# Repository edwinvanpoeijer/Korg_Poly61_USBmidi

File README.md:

# Korg_Poly61_USBmidi
USB Midi conversion for the Korg Poly61 synthesizer

This midi conversion uses a Teensy V3.2 to interface between the keys, arpeggiator and the cpu board.
This will add the following functionality to your Korg Poly61:

USB Midi interface
Hardware MIDI input
Hardware MIDI thru (from the hardware MIDI input)
Hardware MIDI out/thru (forwarded from the USB midi) 
MIDI synced arpeggiator (can be set to internal,  1/4, 1/8, 1/16, 1/32)
SYNC/TRIGGER out 
MIDI port selectable (1 - 16 or OMNI)

The MIDI port and arpeggiator sync can be set at power on by holding the keys.
C0  = ARP internal
C#0 = ARP 1/4
D0  = ARP 1/8
D#0 = ARP 1/16
E0  = ARP 1/32

C2 = MIDI channel 1 ---> D#3 = MIDI channel 16
E3 = OMNI

I have included the code, schematic and a very raw pcb (i still have some available).
There is a lot of space between the components and the pcb could be half it's current size :)
You will need a Teensy 3.1/3.2 for this as these are still 5V tolerant.

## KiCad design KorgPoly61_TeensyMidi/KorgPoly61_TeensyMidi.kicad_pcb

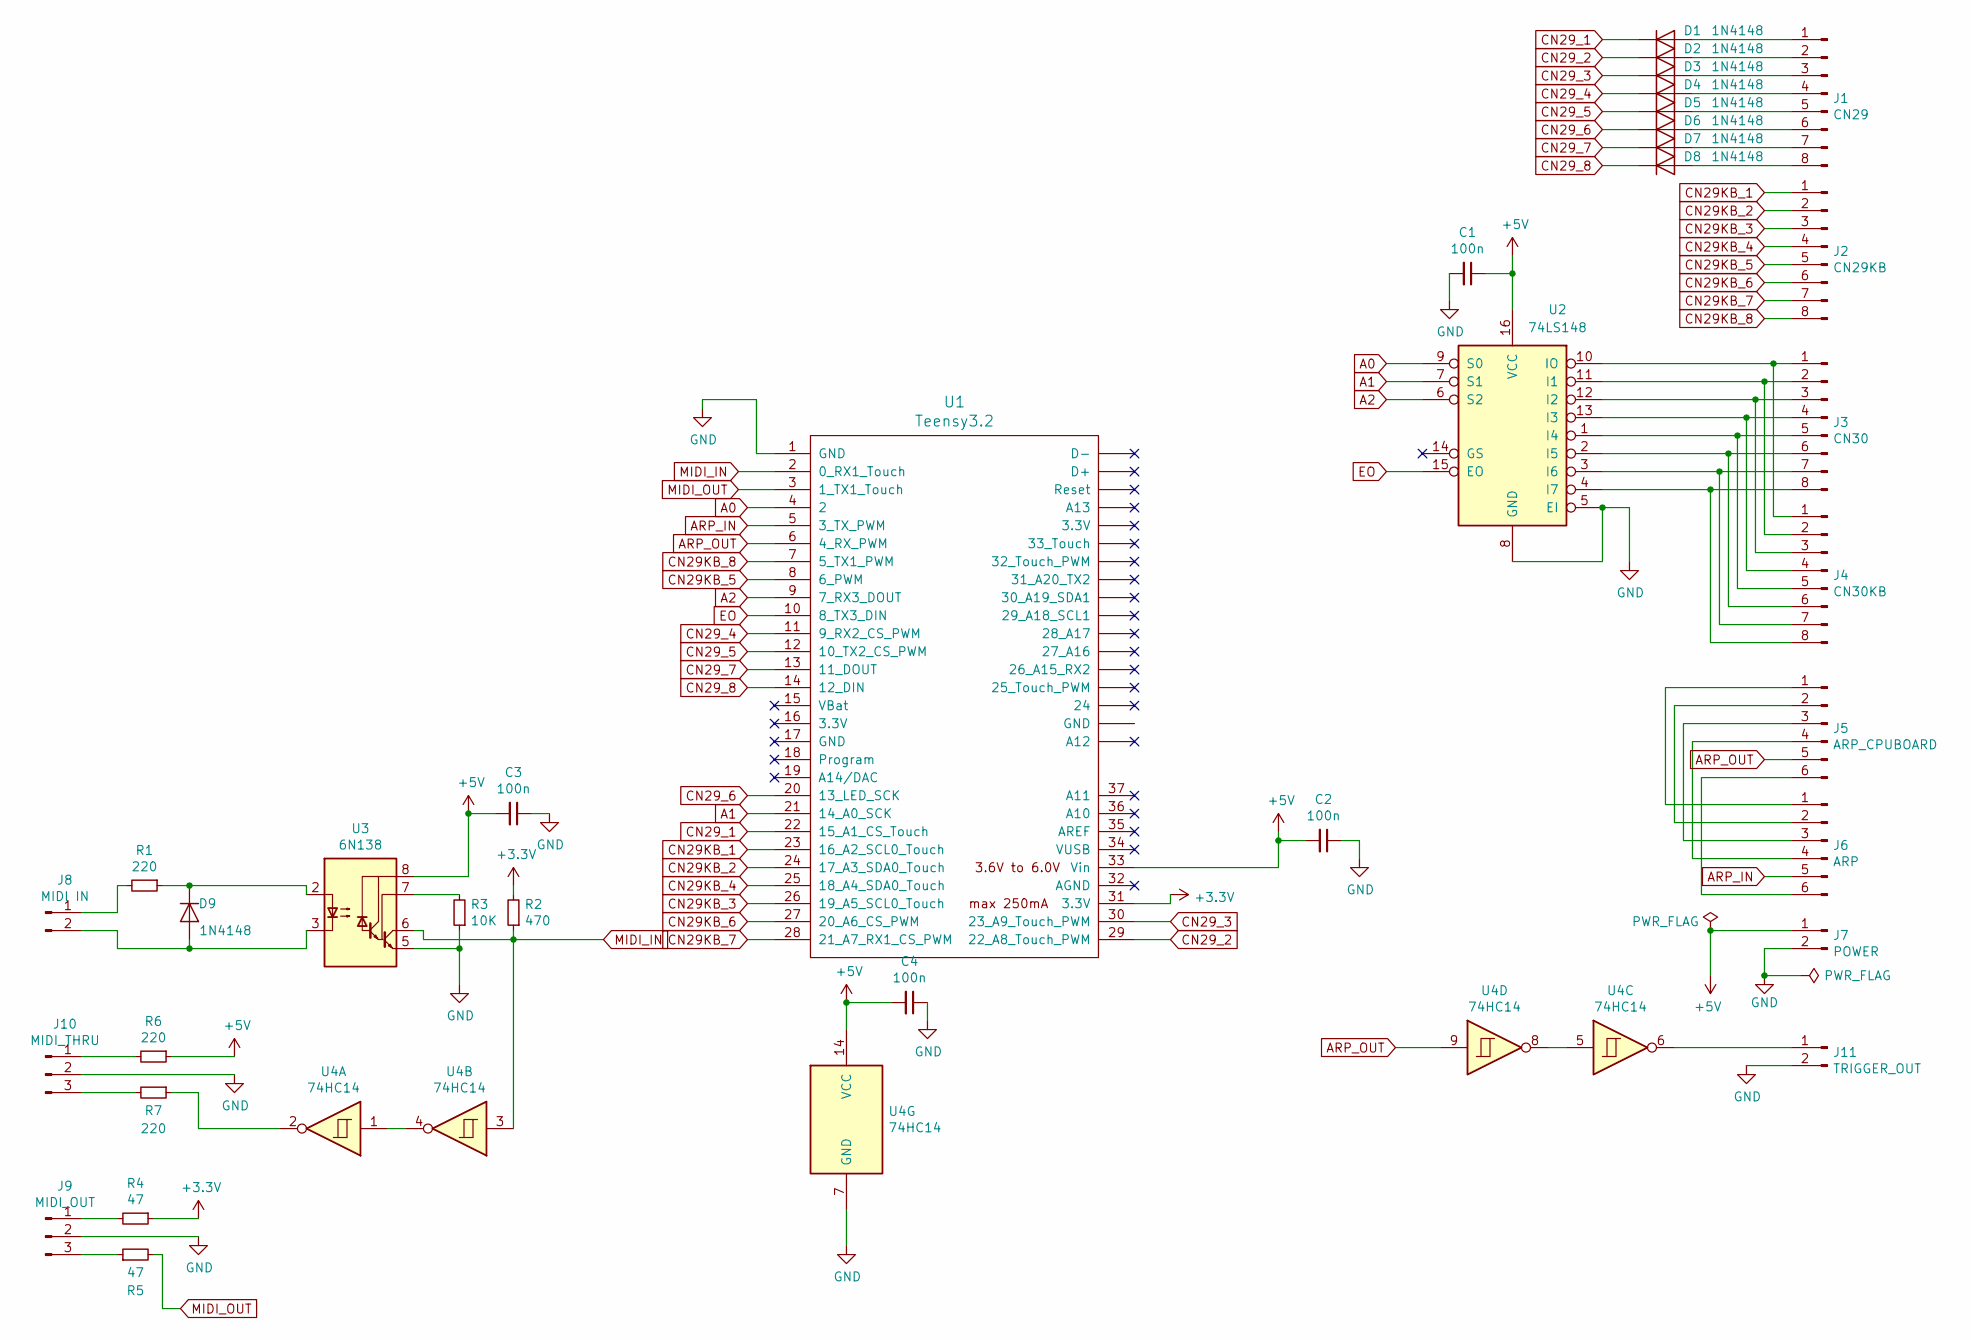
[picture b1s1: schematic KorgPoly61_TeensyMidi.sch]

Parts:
C1, C2, C3, C4: 100n; C_Disc_D5.0mm_W2.5mm_P5.00mm
D1, D2, D3, D4, D5, D6, D7, D8, D9: 1N4148; D_DO-15_P10.16mm_Horizontal
J1: CN29; PinHeader_1x08_P2.54mm_Vertical
J2: CN29KB; PinHeader_1x08_P2.54mm_Vertical
J3: CN30; PinHeader_1x08_P2.54mm_Vertical
J4: CN30KB; PinHeader_1x08_P2.54mm_Vertical
J5: ARP_CPUBOARD; PinHeader_1x06_P2.54mm_Vertical
J6: ARP; PinHeader_1x06_P2.54mm_Vertical
J7: POWER; PinHeader_1x02_P2.54mm_Vertical
J8: MIDI IN; PinHeader_1x02_P2.54mm_Vertical
J9: MIDI_OUT; PinHeader_1x03_P2.54mm_Vertical
J10: MIDI_THRU; PinHeader_1x03_P2.54mm_Vertical
J11: TRIGGER_OUT; PinHeader_1x02_P2.54mm_Vertical
R1, R6, R7: 220; R_Axial_DIN0207_L6.3mm_D2.5mm_P7.62mm_Horizontal
R2: 470; R_Axial_DIN0207_L6.3mm_D2.5mm_P7.62mm_Horizontal
R3: 10K; R_Axial_DIN0207_L6.3mm_D2.5mm_P7.62mm_Horizontal
R4, R5: 47; R_Axial_DIN0207_L6.3mm_D2.5mm_P7.62mm_Horizontal
U1: Teensy3.2; Teensy30_31_32_LC
U2: 74LS148; DIP-16_W7.62mm_Socket
U3: 6N138; DIP-8_W7.62mm
U4: 74HC14; DIP-14_W7.62mm_Socket

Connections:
+3V3: R2.2, R4.1, U1.31 (3.3V)
+5V: C1.1, C2.2, C3.2, C4.2, J7.1, R6.1, U1.33 (Vin), U2.16 (VCC), U3.8 (VCC), U4.14 (VCC)
A0: U1.4 (2), U2.9 (S0)
A1: U1.21 (14_A0_SCK), U2.7 (S1)
A2: U1.9 (7_RX3_DOUT), U2.6 (S2)
ARP_IN: J6.5, U1.5 (3_TX_PWM)
ARP_OUT: J5.5, U1.6 (4_RX_PWM), U4.9
CN29KB_1: J2.1, U1.23 (16_A2_SCL0_Touch)
CN29KB_2: J2.2, U1.24 (17_A3_SDA0_Touch)
CN29KB_3: J2.3, U1.26 (19_A5_SCL0_Touch)
CN29KB_4: J2.4, U1.25 (18_A4_SDA0_Touch)
CN29KB_5: J2.5, U1.8 (6_PWM)
CN29KB_6: J2.6, U1.27 (20_A6_CS_PWM)
CN29KB_7: J2.7, U1.28 (21_A7_RX1_CS_PWM)
CN29KB_8: J2.8, U1.7 (5_TX1_PWM)
CN29_1: D1.1 (K), U1.22 (15_A1_CS_Touch)
CN29_2: D2.1 (K), U1.29 (22_A8_Touch_PWM)
CN29_3: D3.1 (K), U1.30 (23_A9_Touch_PWM)
CN29_4: D4.1 (K), U1.11 (9_RX2_CS_PWM)
CN29_5: D5.1 (K), U1.12 (10_TX2_CS_PWM)
CN29_6: D6.1 (K), U1.20 (13_LED_SCK)
CN29_7: D7.1 (K), U1.13 (11_DOUT)
CN29_8: D8.1 (K), U1.14 (12_DIN)
EO: U1.10 (8_TX3_DIN), U2.15 (EO)
GND: C1.2, C2.1, C3.1, C4.1, J7.2, J9.2, J10.2, J11.2, R3.1, U1.1 (GND), U2.5 (EI), U2.8 (GND), U3.5 (GND), U4.7 (GND)
MIDI_IN: R2.1, U1.2 (0_RX1_Touch), U3.6 (VO2), U4.3
MIDI_OUT: R5.2, U1.3 (1_TX1_Touch)
unnamed: D1.2 (A), J1.1
unnamed: D2.2 (A), J1.2
unnamed: D3.2 (A), J1.3
unnamed: D4.2 (A), J1.4
unnamed: D5.2 (A), J1.5
unnamed: D6.2 (A), J1.6
unnamed: D7.2 (A), J1.7
unnamed: D8.2 (A), J1.8
unnamed: D9.1 (K), R1.1, U3.2 (C1)
unnamed: D9.2 (A), J8.2, U3.3 (C2)
unnamed: J3.1, J4.1, U2.10 (IO)
unnamed: J3.2, J4.2, U2.11 (I1)
unnamed: J3.3, J4.3, U2.12 (I2)
unnamed: J3.4, J4.4, U2.13 (I3)
unnamed: J3.5, J4.5, U2.1 (I4)
unnamed: J3.6, J4.6, U2.2 (I5)
unnamed: J3.7, J4.7, U2.3 (I6)
unnamed: J3.8, J4.8, U2.4 (I7)
unnamed: J5.1, J6.1
unnamed: J5.2, J6.2
unnamed: J5.3, J6.3
unnamed: J5.4, J6.4
unnamed: J5.6, J6.6
unnamed: J8.1, R1.2
unnamed: J9.1, R4.2
unnamed: J9.3, R5.1
unnamed: J10.1, R6.2
unnamed: J10.3, R7.2
unnamed: J11.1, U4.6
unnamed: R3.2, U3.7 (VO1)
unnamed: R7.1, U4.2
unnamed: U4.1, U4.4
unnamed: U4.5, U4.8

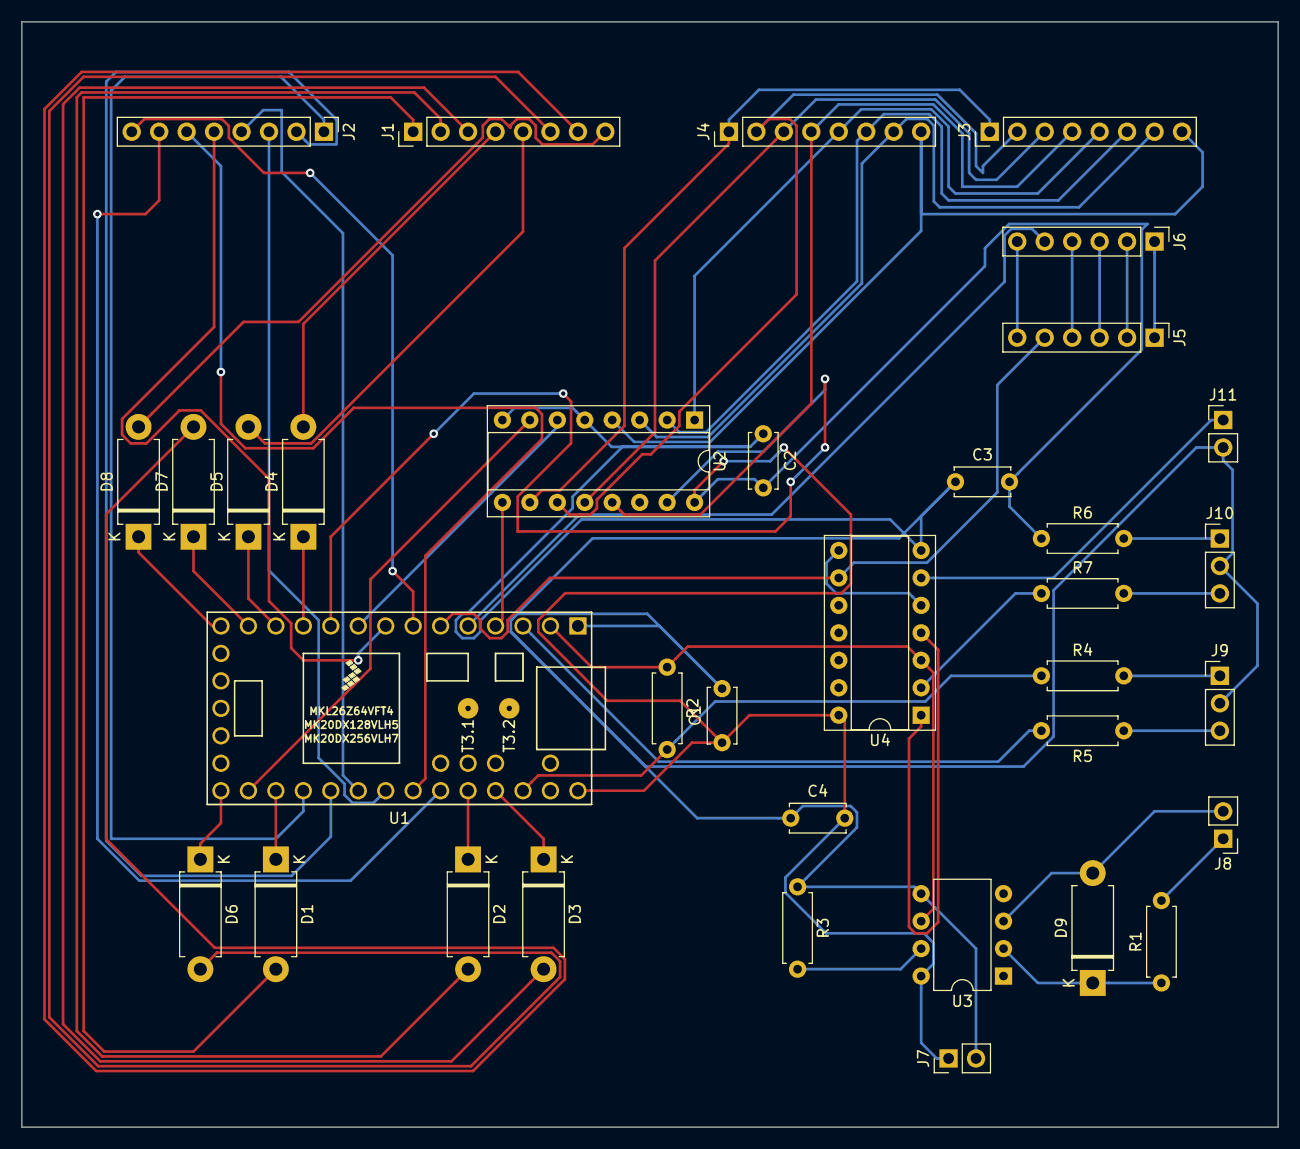
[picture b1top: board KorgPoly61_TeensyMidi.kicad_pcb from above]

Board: 2 copper layers, 116.2 x 102.2 mm, 35 parts (0 on the bottom side), 60 nets.

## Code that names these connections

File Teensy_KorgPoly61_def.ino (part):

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
// Output (CN29) = PORT c
const byte CN29_0 = 15;
const byte CN29_1 = 22;
const byte CN29_2 = 23;
const byte CN29_3 = 9;
const byte CN29_4 = 10;
const byte CN29_5 = 13;
const byte CN29_6 = 11;
const byte CN29_7 = 12;

// Input (CN30) = PORT D
const byte CN30_0 = 2;
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
  // Set CN29 to output
  pinMode( CN29_0, OUTPUT);
  pinMode( CN29_1, OUTPUT);
  pinMode( CN29_2, OUTPUT);
  pinMode( CN29_3, OUTPUT);
  pinMode( CN29_4, OUTPUT);
  pinMode( CN29_5, OUTPUT);
  pinMode( CN29_6, OUTPUT);
  pinMode( CN29_7, OUTPUT);

  pinMode(arpIn, INPUT_PULLUP);
  pinMode(arpOut, OUTPUT);
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

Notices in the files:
Teensy_KorgPoly61_def.ino:
This example code is in the public domain.
